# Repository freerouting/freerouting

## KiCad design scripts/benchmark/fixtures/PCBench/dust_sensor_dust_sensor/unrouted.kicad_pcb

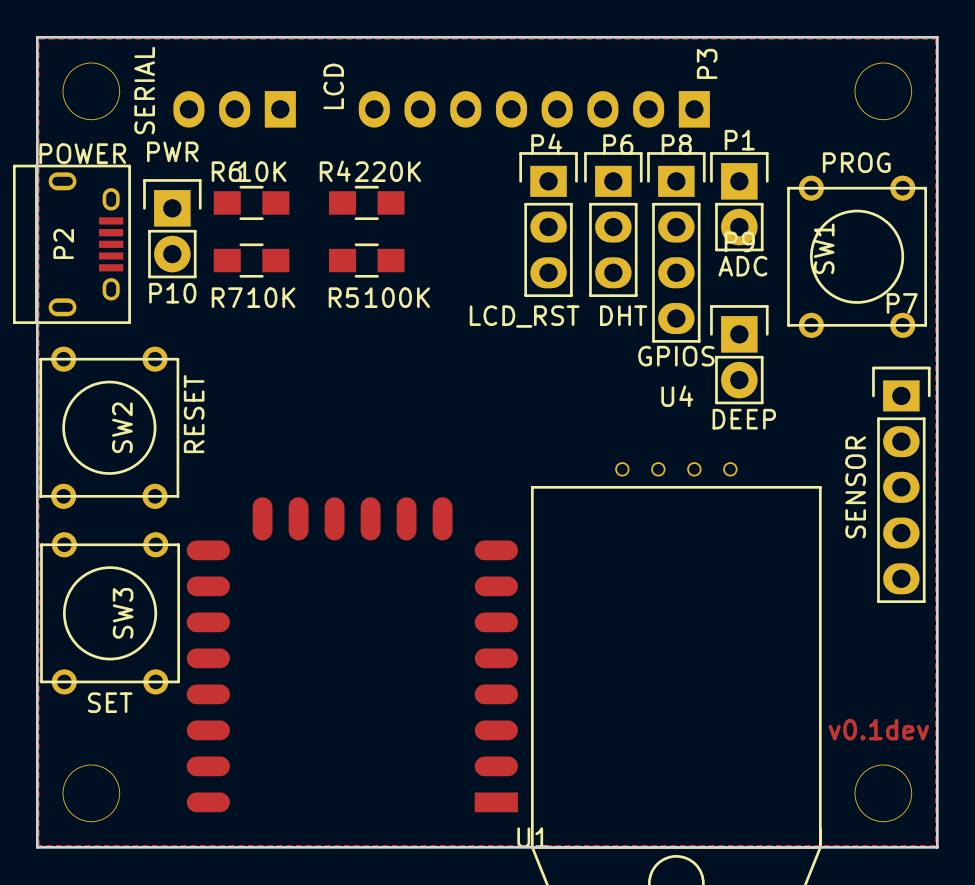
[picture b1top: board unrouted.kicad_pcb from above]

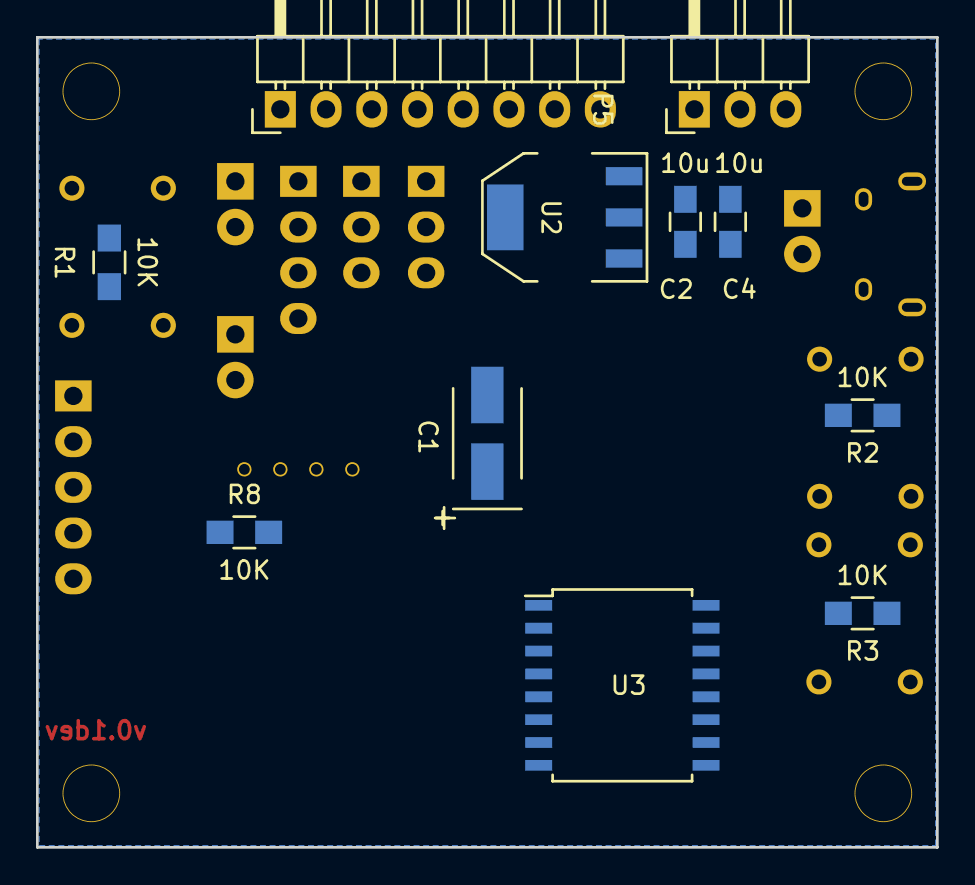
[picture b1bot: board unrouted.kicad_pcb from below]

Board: 2 copper layers, 50.0 x 45.0 mm, 32 parts (11 on the bottom side), 29 nets, no tracks yet.

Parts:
C1: 100u; TantalC_SizeB_EIA-3528_HandSoldering
C2, C4: 10u; C_0805_HandSoldering
Noname_1, Noname_2, Noname_3, Noname_4: hole_3mm
P1: ADC; Pin_Header_Straight_1x02
P2: POWER; USB_Micro-B
P3: LCD; Pin_Header_Angled_1x08
P4: LCD_RST; Pin_Header_Straight_1x03
P5: SERIAL; Pin_Header_Angled_1x03
P6: DHT; Pin_Header_Straight_1x03
P7: SENSOR; Pin_Header_Straight_1x05
P8: GPIOS; Pin_Header_Straight_1x04
P9: DEEP; Pin_Header_Straight_1x02
P10: PWR; Pin_Header_Straight_1x02
R1, R2, R3, R6, R7, R8: 10K; R_0805_HandSoldering
R4: 220K; R_0805_HandSoldering
R5: 100K; R_0805_HandSoldering
SW1: PROG; SW_PUSH_SMALL
SW2: RESET; SW_PUSH_SMALL
SW3: SET; SW_PUSH_SMALL
U1: ESP-12E
U2: AP1117; SOT-223
U3: PCF8574; SOIC-16_7.5x10.3mm_Pitch1.27mm
U4: DHT22; DHT22_nohole

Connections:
+3V3: C1.1, C4.1, P3.6, R1.1, R2.1, R3.1, R6.2, R8.1, U1.8, U2.2, U3.16, U4.1
+5V: P2.1, P7.4, P10.2
ADC: R4.2, R5.1, U1.2
DHT_EXT: P6.3, U3.6
DHT_GPIO: P6.1, P8.1, U1.5
GND: C1.2, C2.2, C4.2, P1.2, P2.5, P3.2, P3.8, P5.3, P7.3, R5.2, R7.2, SW1.2, SW2.2, SW3.2, U1.15, U2.1, U3.1, U3.2, U3.3, U3.8, U4.4
GPIO16: P9.2, U1.4
LIGHT: P3.7, U3.4
unnamed: C2.1, P10.1, U2.3
unnamed: P1.1, R4.1
unnamed: P3.1, P4.2
unnamed: P3.3, U3.11
unnamed: P3.4, U1.6
unnamed: P3.5, U1.7
unnamed: P4.1, U3.12
unnamed: P6.2, R8.2, U4.2
unnamed: R6.1, U1.3
unnamed: R7.1, U1.16
unnamed: U1.17, U3.13
unnamed: U1.19, U3.15
unnamed: U1.20, U3.14
P3: P8.4, U3.7
P4: P8.3, U3.9
P5: P8.2, U3.10
PROG: R1.2, SW1.1, U1.18
RESET: P4.3, P9.1, R2.2, SW2.1, U1.1
RX: P5.2, P7.1, U1.21
SET: R3.2, SW3.1, U3.5
TX: P5.1, P7.2, U1.22

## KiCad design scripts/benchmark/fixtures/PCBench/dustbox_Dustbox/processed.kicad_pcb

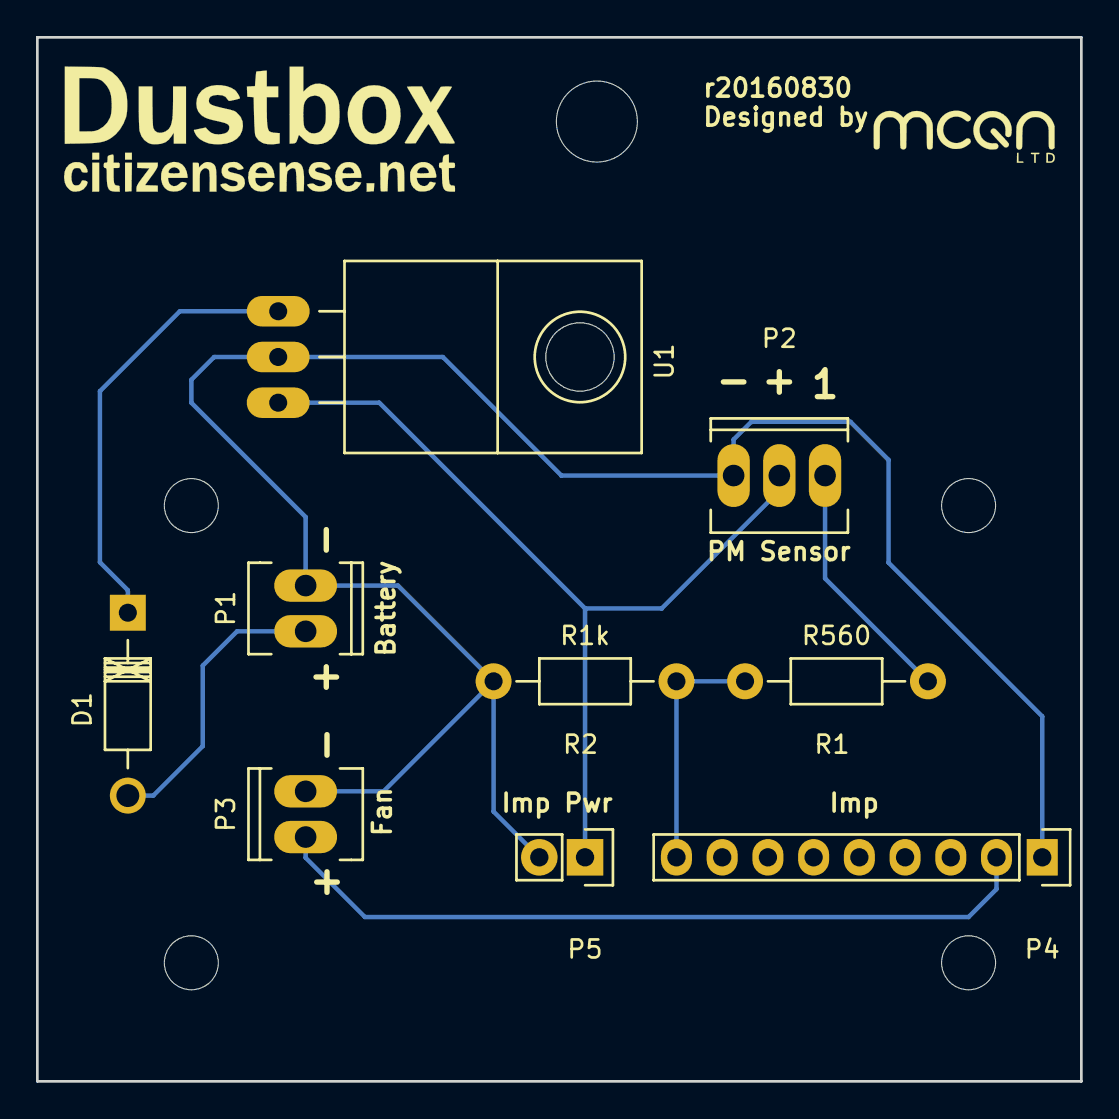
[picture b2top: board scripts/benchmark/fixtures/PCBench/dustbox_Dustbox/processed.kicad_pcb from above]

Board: 2 copper layers, 58.0 x 58.0 mm, 9 parts (0 on the bottom side), 7 nets.

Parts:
D1: 1N5817; Diode_DO-41_SOD81_Horizontal_RM10
P1: CONN_BATT; Socket_MOLEX-KK-RM2-54mm_Lock_2pin_straight
P2: CONN_PM2.5_SENSOR; Socket_MOLEX-KK-RM2-54mm_Lock_3pin_straight
P3: CONN_FAN; Socket_MOLEX-KK-RM2-54mm_Lock_2pin_straight
P4: CONN_APRIL_IMP; Socket_Strip_Straight_1x09
P5: CONN_APRIL_POWER; Socket_Strip_Straight_1x02
R1: R560; Resistor_Horizontal_RM10mm
R2: R1k; Resistor_Horizontal_RM10mm
U1: LF50CV; TO-220_Regulator_Horizontal_LargePads

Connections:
unnamed: D1.1, U1.VI
unnamed: D1.2, P1.2
unnamed: P1.1, P2.1, P3.2, P4.1, P5.2, R2.2, U1.GND
unnamed: P2.2, P5.1, U1.VO
unnamed: P2.3, R1.1
unnamed: P3.1, P4.2
unnamed: P4.9, R1.2, R2.1

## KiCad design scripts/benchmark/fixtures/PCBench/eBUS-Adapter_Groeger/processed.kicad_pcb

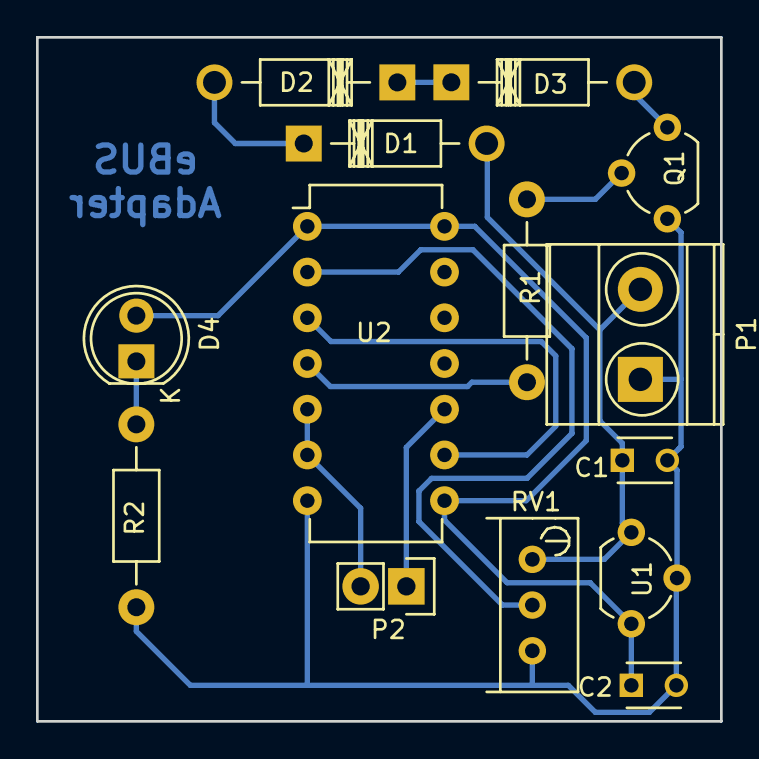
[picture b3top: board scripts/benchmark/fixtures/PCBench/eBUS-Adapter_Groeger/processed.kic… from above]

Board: 2 copper layers, 38.0 x 38.0 mm, 14 parts (0 on the bottom side), 13 nets.

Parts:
C1, C2: 100pF; C_Disc_D3_P2.5
D1, D2: 1N4148; Diode_DO-41_SOD81_Horizontal_RM10
D3: 7.5V/1.3W; Diode_DO-41_SOD81_Horizontal_RM10
D4: LED; LED-5MM
P1: EBUS; TerminalBlock_Pheonix_MKDS1.5-2pol
P2: RS232; Pin_Header_Straight_1x02
Q1: PN2222A; TO-92_Molded_Wide
R1: 8k; Resistor_Horizontal_RM10mm
R2: 470; Resistor_Horizontal_RM10mm
RV1: 10k; Potentiometer_Bourns_3296W_3-8Zoll_Inline_ScrewUp
U1: 7805; TO-92_Molded_Wide
U2: 4011; DIP-14_W7.62mm

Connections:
EBUS+: C1.1, D1.2, P1.2, RV1.1, U1.1
EBUS-: C1.2, C2.2, P1.1, Q1.1, R2.2, RV1.3, U1.2, U2.7
unnamed: D1.1, D2.2
unnamed: D2.1, D3.1
unnamed: D3.2, Q1.3
unnamed: D4.1, R2.1
unnamed: Q1.2, R1.1
unnamed: R1.2, U2.4
unnamed: RV1.2, U2.2
unnamed: U2.3, U2.9
RXD: P2.1, U2.10
TXD: P2.2, U2.5, U2.6
VDD: C2.1, D4.2, U1.3, U2.1, U2.8, U2.14

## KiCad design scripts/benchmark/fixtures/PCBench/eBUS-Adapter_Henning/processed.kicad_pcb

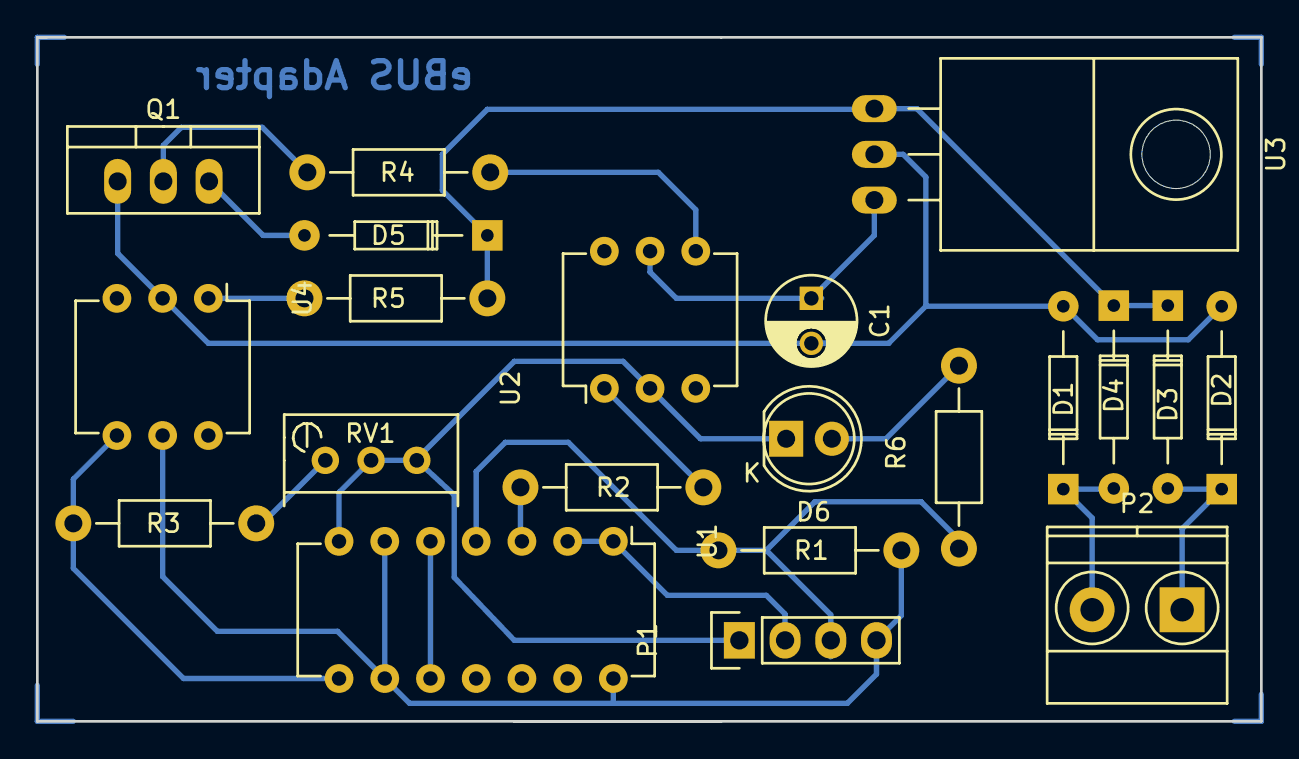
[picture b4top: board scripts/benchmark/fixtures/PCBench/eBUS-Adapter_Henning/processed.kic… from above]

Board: 2 copper layers, 68.0 x 38.0 mm, 21 parts (0 on the bottom side), 19 nets.

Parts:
C1: CP; C_Radial_D5_L6_P2.5
D1, D2, D3, D4: 1N4148; Diode_DO-35_SOD27_Horizontal_RM10
D5: ZPY7.5V 1.3W; Diode_DO-35_SOD27_Horizontal_RM10
D6: LED; LED-5MM
P1: RS232; Pin_Header_Straight_1x04
P2: EBUS; TerminalBlock_Pheonix_MKDS1.5-2pol
Q1: BD645; TO-220_Neutral123_Vertical
R1: 10k; Resistor_Horizontal_RM10mm
R2: 470; Resistor_Horizontal_RM10mm
R3, R6: 1k; Resistor_Horizontal_RM10mm
R4: 22k; Resistor_Horizontal_RM10mm
R5: 3k3; Resistor_Horizontal_RM10mm
RV1: 20k; Potentiometer_Bourns_3296W_3-8Zoll_Inline_ScrewUp
U1: 4011; DIP-14_W7.62mm
U2, U4: CNY17-1; DIP-6_W7.62mm
U3: 78L05; TO-220_Neutral123_Horizontal

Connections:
EBUS1: D1.1, D4.2, P2.2
EBUS2: D2.1, D3.2, P2.1
GND: D6.1, P1.1, RV1.2, RV1.3, U1.7, U2.2
unnamed: C1.1, U2.5, U3.3
unnamed: C1.2, D1.2, D2.2, Q1.1, U3.2, U4.2
unnamed: D3.1, D4.1, D5.1, R5.1, U3.1
unnamed: D5.2, Q1.3
unnamed: D6.2, R6.2
unnamed: Q1.2, R4.1
unnamed: R2.1, U2.1
unnamed: R2.2, U1.3
unnamed: R3.1, U1.8, U4.4
unnamed: R3.2, RV1.1
unnamed: R4.2, U2.4
unnamed: R5.2, U4.1
unnamed: U1.5, U1.10
RXD: P1.3, R1.2, R6.1, U1.4
TXD: P1.2, U1.1, U1.2
VDD: P1.4, R1.1, U1.6, U1.9, U1.14, U4.5
